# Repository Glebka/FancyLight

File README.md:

# FancyLight

FancyLight - an LED lamp powered by a Li-Ion battery, which can be found in used electronic cigarettes. It charges via a micro USB connector and is turned on and off using a touch button. A simple project to learn how to work with the TP4056 battery charging controller, a step-up DC-DC converter based on the SB6286 for powering LEDs, a touch switch controller based on the TTP223-BA6, as well as battery protection elements based on the DW01-P and dual MOSFET 8205A.

A touch switch controller is assembled on a separate PCB to improve touch sensing reliability.

## TODO

* Fix schematic and PCB:
    * Connect Q1's (SENSE) gate to GND via resistor
* Fix enclosure
    * Design mounting for the PCB for easier assembly
    * Fix the depth of mode selection pocket
    * Adjust heights because of PCB thickness increase
* (Minor) Update schematic and PCB
    * Introduce nRF module for BLE
    * Add wireless charger receiver as an alternative to USB-C

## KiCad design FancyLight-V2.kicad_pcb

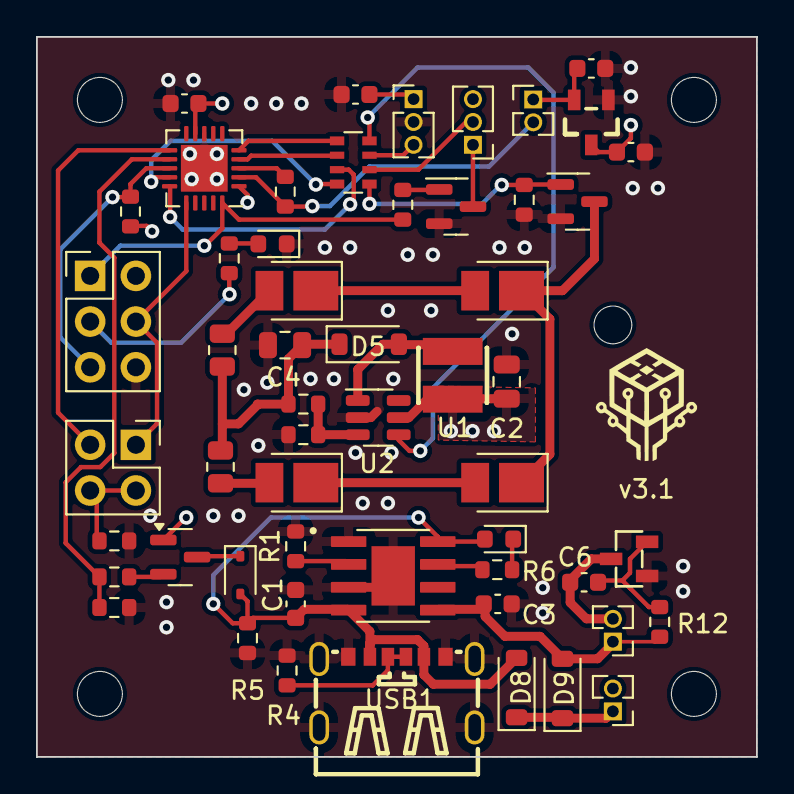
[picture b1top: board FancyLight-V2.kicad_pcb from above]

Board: 4 copper layers, 40.0 x 40.0 mm, 59 parts (0 on the bottom side), 42 nets.

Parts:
BT1: 1000 mAh; PinHeader_1x02_P1.27mm_Vertical
C1, C3, C5, C7, C8: 10u; C_0603_1608Metric
C2, C4: 22uF; C_0805_2012Metric
C6, C9: 0.1u; C_0603_1608Metric
D1, D2, D3, D4: LED; LED_PLCC_2835_Handsoldering
D5, D8, D9: B5819W SL; D_SOD-123
D6: 1N5819WS; D_SOD-323
D7: CHRG LED; LED_0603_1608Metric
D10: STATUS LED; LED_0603_1608Metric
H1, H2, H3, H4: MountingHole_2.5mm
H5: MountingHole_2.1mm
J1: ISP; PinHeader_2x03_P2.54mm_Vertical
J2: TOUCH; PinHeader_1x03_P1.27mm_Vertical
J3: MODE; PinHeader_2x02_P2.54mm_Vertical
Q1, Q2, Q3: AO3400A; SOT-23
R1: 3k; R_0603_1608Metric
R2, R3: 22; R_0805_2012Metric
R4: 5.1k; R_0603_1608Metric
R5, R6, R12: 1k; R_0603_1608Metric
R7, R9: 100k; R_0603_1608Metric
R8, R10, R11, R14, R17, R18: 10k; R_0603_1608Metric
R13: 5k; R_0603_1608Metric
R15: 330; R_0603_1608Metric
R16: R_Photo; PinHeader_1x02_P1.27mm_Vertical
RN1: 470; R_Array_Convex_4x0603
SW1: ONOFF; PinHeader_1x02_P1.27mm_Vertical
U1: APSWPA3015S4R7MTF; IND-SMD_L3.0-W3.0
U2: SB6286; SOT-23-6
U3: TP4056; SOP127P600X175-9N
U4: XB3303A; SOT-23-3_L2.9-W1.3-P1.90-LS2.4-BR
U5: HT7530S_C5451677; SOT-23-3_L2.9-W1.3-P1.90-LS2.4-BR-CW
U6: ATtiny44A-M; QFN-20-1EP_4x4mm_P0.5mm_EP2.6x2.6mm
U7: syn480r; PinHeader_1x03_P1.27mm_Vertical
USB1: TYPE-C_6P; TYPE-C-SMD_TYPE-C-6P

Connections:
3V: C7.1, C8.1, J2.1, R16.1, U5.3 (VOUT)
BAT+: BT1.1 (+), C3.1, D9.2 (A), R12.1, U3.5 (BAT)
BAT-: C1.2, C2.1, C3.2, C4.2, C5.2, C7.2, C8.2, C9.1, D10.1 (K), J1.6, J2.2, Q2.2 (S), Q3.2 (S), R1.2, R4.2, R5.1, R8.2, R9.2, R11.2, R18.1, U2.2 (GND), U3.1 (TEMP), U3.3 (GND), U3.9 (EP), U4.1 (VM), U5.1 (GND), U6.8 (GND), U6.21 (GND), USB1.7 (EH), USB1.A12 (GND), USB1.B12 (GND)
DCDC_EN: RN1.8 (R1.2), U2.4 (EN)
DRAIN: D3.1 (K), D4.1 (K), Q2.3 (D)
LED_PWR: C4.1, D5.1 (K), R2.2, R3.2, R7.1
MISO: J1.1, R15.2, U6.20 (PA5)
MODE1: J1.4, J3.1, U6.16 (PA6)
MODE2: J3.3, U6.11 (XTAL1/PB0)
unnamed: BT1.2 (-), C6.2, U4.3 (GND)
unnamed: D1.2 (A), R2.1
unnamed: D1.1 (K), D3.2 (A)
unnamed: D2.2 (A), R3.1
unnamed: D2.1 (K), D4.2 (A)
unnamed: D5.2 (A), U1.2, U2.1 (SW)
unnamed: C1.1, D6.2 (A), D7.2 (A), D8.2 (A), R5.2, U3.4 (VCC), U3.8 (CE), USB1.A9 (VBUS), USB1.B9 (VBUS)
unnamed: D6.1 (K), Q1.3 (D)
unnamed: D7.1 (K), R6.2
unnamed: D8.1 (K), D9.1 (K), SW1.1 (A)
unnamed: D10.2 (A), R13.2
unnamed: J3.2, J3.4, R18.2
unnamed: Q1.2 (S), R10.1
unnamed: Q3.3 (D), U7.1 (GND)
unnamed: RN1.1 (R1.1), U6.5 (AREF/PA0)
unnamed: RN1.2 (R2.1), U6.4 (PA1)
unnamed: RN1.3 (R3.1), U6.15 (PA7)
unnamed: RN1.4 (R4.1), U6.14 (PB2)
unnamed: R7.2, R8.1, U2.3 (FB)
unnamed: R1.1, U3.2 (PROG)
unnamed: R6.1, U3.7 (~CHRG)
unnamed: C6.1, R12.2, U4.2 (VDD)
unnamed: R17.2, U6.3 (PA2)
unnamed: R16.2, R17.1, U6.2 (PA3)
unnamed: R4.1, USB1.A5 (CC1), USB1.B5 (CC2)
PWM: Q2.1 (G), R9.1, RN1.5 (R4.2)
RST: J1.5, R14.1, U6.13 (~RESET/PB3)
R_EN: Q3.1 (G), R15.1
R_TRIG: RN1.6 (R3.2), U7.2 (DAT)
SCK: J1.3, R13.1, U6.1 (PA4)
SENSE: R10.2, R11.1, U6.12 (XTAL2/PB1)
TRIG: J2.3, RN1.7 (R2.2)
VBAT: C2.2, C5.1, C9.2, J1.2, Q1.1 (G), R14.2, SW1.2 (B), U1.1, U2.5 (IN), U5.2 (VIN), U6.9 (VCC), U7.3 (VCC)

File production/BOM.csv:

"Designator","Comment","Footprint","LCSC"
"C1,C3,C5,C7,C8","10u","Capacitor_SMD:C_0603_1608Metric","C96446"
"C2,C4","22uF","Capacitor_SMD:C_0805_2012Metric","C45783"
"C6,C9","0.1u","Capacitor_SMD:C_0603_1608Metric","C14663"
"D1,D2,D3,D4","LED","LED_SMD:LED_PLCC_2835_Handsoldering","C210310"
"D5,D8,D9","B5819W SL","Diode_SMD:D_SOD-123","C8598"
"D6","1N5819WS","Diode_SMD:D_SOD-323","C191023"
"D7","CHRG LED","LED_SMD:LED_0603_1608Metric","C2286"
"D10","STATUS LED","LED_SMD:LED_0603_1608Metric","C2286"
"Q1,Q2","AO3400A","Package_TO_SOT_SMD:SOT-23","C20917"
"R1","3k","Resistor_SMD:R_0603_1608Metric","C4211"
"R2,R3","22","Resistor_SMD:R_0805_2012Metric","C17561"
"R4","5.1k","Resistor_SMD:R_0603_1608Metric","C23186"
"R5,R6,R12","1k","Resistor_SMD:R_0603_1608Metric","C21190"
"R7,R9","100k","Resistor_SMD:R_0603_1608Metric","C25803"
"R8,R10,R11,R14,R17,R18","10k","Resistor_SMD:R_0603_1608Metric","C25804"
"R13","5k","Resistor_SMD:R_0603_1608Metric","C23186"
"R15","330","Resistor_SMD:R_0603_1608Metric","C23138"
"RN1","470","Resistor_SMD:R_Array_Convex_4x0603","C25510"
"U1","APSWPA3015S4R7MTF","kicad_lceda:IND-SMD_L3.0-W3.0","C5363870"
"U2","SB6286","Package_TO_SOT_SMD:SOT-23-6","C157668"
"U3","TP4056","TP4056:SOP127P600X175-9N","C16581"
"U4","XB3303A","kicad_lceda:SOT-23-3_L2.9-W1.3-P1.90-LS2.4-BR","C154937"
"U5","HT7530S_C5451677","kicad_lceda:SOT-23-3_L2.9-W1.3-P1.90-LS2.4-BR-CW","C5451677"
"U6","ATtiny44A-M","Package_DFN_QFN:QFN-20-1EP_4x4mm_P0.5mm_EP2.6x2.6mm","C123718"
"USB1","TYPE-C_6P","kicad_lceda:TYPE-C-SMD_TYPE-C-6P","C456012"

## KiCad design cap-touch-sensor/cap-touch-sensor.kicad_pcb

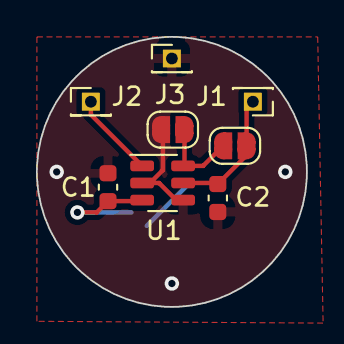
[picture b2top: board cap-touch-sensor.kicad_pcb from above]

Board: 2 copper layers, 15.0 x 15.0 mm, 9 parts (1 on the bottom side), 5 nets.

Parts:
C1: 5-10pF; C_0603_1608Metric
C2: 0.1u; C_0603_1608Metric
J1: VBAT; PinHeader_1x01_P1.27mm_Vertical
J2: TOG; PinHeader_1x01_P1.27mm_Vertical
J3: GND; PinHeader_1x01_P1.27mm_Vertical
JP1, JP2: SolderJumper_2_Open; SolderJumper-2_P1.3mm_Open_RoundedPad1.0x1.5mm
TP4: SENSE; TestPoint_Pad_D4.0mm
U1: TTP223-BA6; SOT-23-6

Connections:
GND: C1.2, C2.2, J3.1, JP2.1 (A), U1.2 (VSS), U1.4 (AHLB)
unnamed: JP1.1 (A), JP2.2 (B), U1.6 (TOG)
unnamed: C1.1, TP4.1, U1.3 (I)
TOGGLE: J2.1, U1.1 (Q)
VBAT: C2.1, J1.1, JP1.2 (B), U1.5 (VDD)

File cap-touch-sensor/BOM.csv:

Comment,Designator,Footprint,LCSC
"5-10pF","C1","Capacitor_SMD:C_0603_1608Metric","C37474"
"0.1u","C2","Capacitor_SMD:C_0603_1608Metric","C14663"
"TTP223-BA6","U1","Package_TO_SOT_SMD:SOT-23-6","C1693666"

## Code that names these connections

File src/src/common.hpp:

#pragma once

// ATtiny44A
// counter-clockwise pinout
#define LED_PIN 6
#define SENSE_PIN 1
#define DCDC_EN_PIN 10
#define PWM_PIN 2
#define TRIGGER_PIN 9
#define PHOTOR_SINK_PIN 8
#define ADC_PIN 7
#define ADC_ANALOG_PIN A3
#define MODE1_PIN 4
#define MODE2_PIN 0
#define LOW_ILLUMINATION_THRESHOLD 15
#define HYSTERESIS 160

namespace event
{
    // Define events
    typedef enum
    {
        BTN_PRESS,
        BTN_RELEASE,
        BTN_LONG_PRESS,
        MAINS_ON,
        MAINS_OFF,
        LOW_ILLUMINATION,
        HIGH_ILLUMINATION,
        WDT_INTERRUPT,
        RF_PACKET_RECEIVED,
        RF_TIMEOUT,
        BRIGHTNESS_LIMIT_REACHED,
        NUM_EVENTS
    } Event;

    extern Event currentEvent;
}

namespace fsm
{
    typedef enum
    {
        OFF,
        PRE_ON1,
        BRIGHTNESS_ADJUSTMENT,
        BRIGHTNESS_LIMIT,
        ON,
        PRE_OFF1,
        NUM_STATES
    } State;
}

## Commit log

2024-03-03 Update CAD files and gitignore
2024-05-18 Change how brightness regulation works
2024-05-24 feat: Add FSM implementation and API functions
2024-05-28 feat: Add power control, config, touch control, brightness control, and illumination control modules
2024-06-08 feat: Update high illumination threshold in illumination control module
2024-06-08 Refactor touch switch controller for improved reliability
2024-07-06 Improve schematic and PCB
2024-07-07 feat: Implement hardware PWM for brightness control
2024-07-07 chore: Update todos
2024-07-07 Update todos again
2025-01-19 feat: Update configuration and enhance brightness control logic
